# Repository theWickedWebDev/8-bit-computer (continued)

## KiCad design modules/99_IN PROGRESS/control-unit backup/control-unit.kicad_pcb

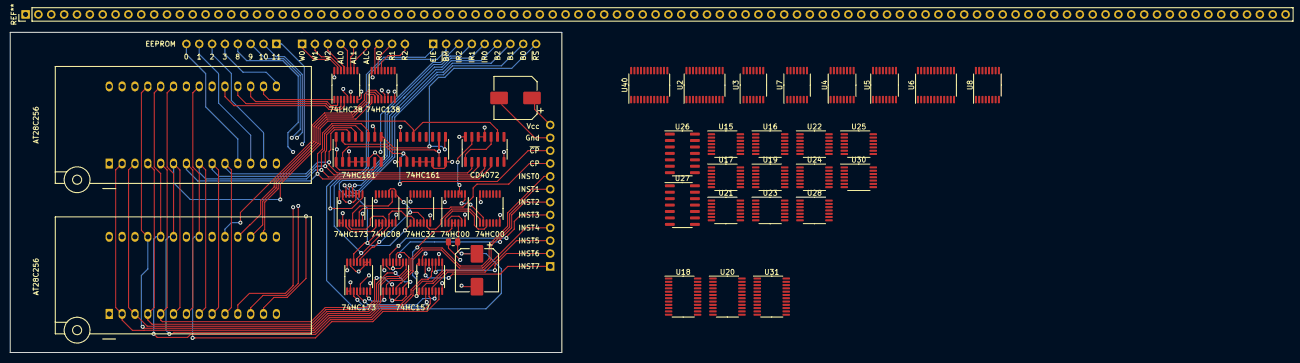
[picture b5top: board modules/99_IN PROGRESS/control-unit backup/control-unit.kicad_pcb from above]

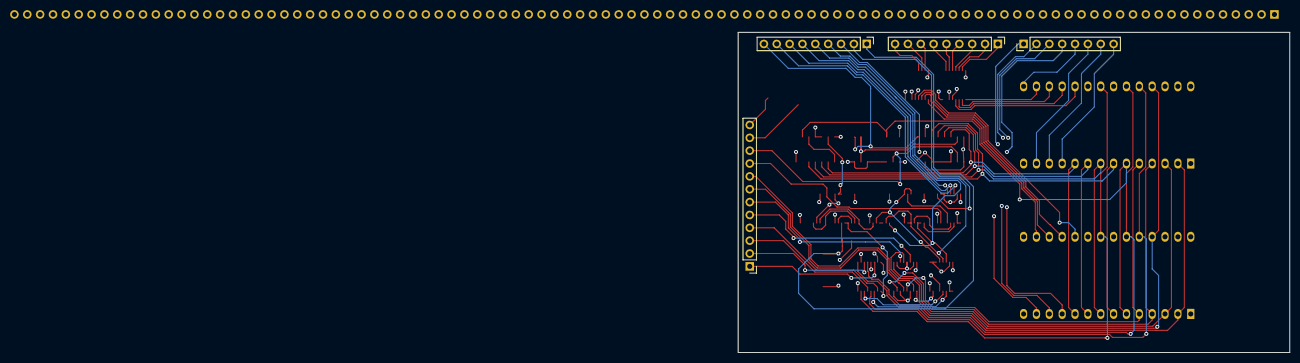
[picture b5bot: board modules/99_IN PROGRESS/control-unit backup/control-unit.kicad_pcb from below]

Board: 4 copper layers, 109.0 x 63.2 mm, 47 parts (4 on the bottom side), 140 nets.

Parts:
C1, C2: CP; CP_Elec_8x10
J1: Conn_01x08; PinHeader_1x08_P2.54mm_Vertical
J2, J3: Conn_01x09; PinHeader_1x09_P2.54mm_Vertical
J4: Conn_01x12; PinHeader_1x12_P2.54mm_Vertical
J5: Conn_01x99; 1x99_pinheader
R1: 3.9kohm; R_0805_2012Metric
U1, U15, U17, U37: 74LS00; TSSOP-14_4.4x5mm_P0.65mm
U2, U6, U18, U20, U31, U40: 74LS154; TSSOP-24_4.4x7.8mm_P0.65mm
U3, U23, U24, U25, U38: 74LS08; TSSOP-14_4.4x5mm_P0.65mm
U4, U5: 74LS258; TSSOP-16_4.4x5mm_P0.65mm
U7: 74HC04; TSSOP-14_4.4x5mm_P0.65mm
U8, U34, U35: 74LS157; TSSOP-16_4.4x5mm_P0.65mm
U9, U12: 28C256; DIP_Socket-28_W11.9_W12.7_W15.24_W17.78_W18.5_3M_228-1277-0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
U10, U11: 74LS161; SOIC-16_3.9x9.9mm_P1.27mm
U13, U14: 74LS138; TSSOP-16_4.4x5mm_P0.65mm
U16, U21: 74LS04; TSSOP-14_4.4x5mm_P0.65mm
U19, U28, U29, U30: 74LS32; TSSOP-14_4.4x5mm_P0.65mm
U22: 74LS86; TSSOP-14_4.4x5mm_P0.65mm
U26, U27, U33: CD4072; SOIC-14_3.9x8.7mm_P1.27mm
U36, U39: 74LS173; TSSOP-16_4.4x5mm_P0.65mm

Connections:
/Conditional Jumps/~JUMP: U6.2, U16.1
/Conditional Jumps/~JUMP_JA_JNBE: U6.13, U21.1
/Conditional Jumps/~JUMP_JBE_JNA: U6.11, U16.13
/Conditional Jumps/~JUMP_JB_JNAE_JC: U6.9, U16.11
/Conditional Jumps/~JUMP_JE_JZ: U6.7, U16.9
/Conditional Jumps/~JUMP_JGE_JNL: U6.15, U21.9
/Conditional Jumps/~JUMP_JG_JNLE: U6.17, U21.13
/Conditional Jumps/~JUMP_JLE_JNG: U6.16, U21.5
/Conditional Jumps/~JUMP_JL_JNG: U6.14, U21.3
/Conditional Jumps/~JUMP_JNB_JAE_JNC: U6.10, U15.12
/Conditional Jumps/~JUMP_JNE_JNZ: U6.8, U15.9
/Conditional Jumps/~JUMP_JNO: U6.4, U15.1
/Conditional Jumps/~JUMP_JNS: U6.6, U15.4
/Conditional Jumps/~JUMP_JO: U6.3, U16.3
/Conditional Jumps/~JUMP_JS: U6.5, U16.5
/GROUP 1/ALU_MODE: J3.4, U3.10, U13.12
/GROUP 1/EEPROM_0: J1.8, U2.23, U6.23, U8.2, U9.11, U40.23
/GROUP 1/EEPROM_1: J1.7, U2.22, U6.22, U8.5, U9.12, U40.22
/GROUP 1/EEPROM_2: J1.6, U2.21, U6.21, U8.11, U9.13, U40.21
/GROUP 1/EEPROM_3: J1.5, U2.20, U6.20, U8.14, U9.15, U40.20
/GROUP 1/SHA_SEL_00: U4.7, U5.7
/GROUP 1/SHA_SEL_01: U4.4, U5.4
/GROUP 1/~ALU_MODE_0_CARRY_IN_EN: J3.6, U3.4, U7.1, U13.10
/GROUP 1/~ALU_MODE_1_EN: J3.5, U3.9, U13.11
/GROUP 1/~WRITE_MUX0_EN: J3.1, U13.15, U40.18, U40.19
/GROUP 1/~WRITE_MUX1_EN: J3.2, U2.18, U2.19, U13.14
/GROUP 1/~WRITE_MUX2_EN: J3.3, U6.18, U6.19, U13.13
/GROUP 2/EEPROM_8: J1.4, U12.11, U18.23, U20.23, U31.23
/GROUP 2/EEPROM_9: J1.3, U12.12, U18.22, U20.22, U31.22
/GROUP 2/EEPROM_10: J1.2, U12.13, U18.21, U20.21, U31.21
/GROUP 2/EEPROM_11: J1.1, U12.15, U18.20, U20.20, U31.20
/GROUP 2/~READ_MUX0_EN: J3.7, U14.15, U18.18, U18.19
/GROUP 2/~READ_MUX1_EN: J3.8, U14.14, U20.18, U20.19
/GROUP 2/~READ_MUX2_EN: J3.9, U14.13, U31.18, U31.19
/MICROCODE EEPROM W/ COUNTER/BUS_0: J2.8, U36.14
/MICROCODE EEPROM W/ COUNTER/BUS_1: J2.7, U36.13
/MICROCODE EEPROM W/ COUNTER/BUS_2: J2.6, U36.12
/MICROCODE EEPROM W/ COUNTER/END_INTERRUPT_ENTER: C2.1, J2.1, R1.1, U37.5
/MICROCODE EEPROM W/ COUNTER/~SET_INT_ENABLE_BITMASK: J2.2, U36.9
CARRY_FLAG: U3.12, U15.13, U17.2, U19.2, U24.13
CLOCK: J4.9, U36.7
EEPROM_4: U9.16, U13.1
EEPROM_5: U9.17, U13.2
EEPROM_6: U9.18, U13.3
EEPROM_7: U9.19, U13.4
EEPROM_12: U12.16, U14.1
EEPROM_13: U12.17, U14.2
EEPROM_14: U12.18, U14.3
EEPROM_15: U12.19, U14.4
GND: C1.2, C2.2, J4.11, U1.7, U2.12, U3.7, U4.2, U4.6, U4.8, U4.10, U4.11, U4.13, U4.14, U5.3, U5.6, U5.8, U5.10, U5.11, U5.13, U5.14, U6.12, U7.7, U8.3, U8.6, U8.8, U8.10, U8.13, U8.15, U9.1, U9.14, U9.20, U9.22, U9.26, U10.3, U10.4, U10.5, U10.6, U10.8, U11.3, U11.4, U11.5, U11.6, U11.8, U12.14, U12.20, U12.22, U12.26, U13.5, U13.8, U14.5, U14.8, U15.7, U16.7, U17.7, U18.12, U19.7, U20.12, U21.7, U22.7, U23.7, U24.7, U25.7, U26.7, U27.7, U28.7, U29.7, U30.7, U31.12, U33.7, U33.11, U33.12, U34.3, U34.6, U34.8, U34.10, U34.13, U34.15, U35.8, U35.15, U36.1, U36.2, U36.8, U36.10, U36.11, U36.15, U37.7, U38.7, U39.1, U39.2, U39.8, U39.9, U39.10, U39.11, U39.15, U40.12
INSTRUCTION_0: J4.8, U34.2
INSTRUCTION_1: J4.7, U34.5
INSTRUCTION_2: J4.6, U34.11
INSTRUCTION_3: J4.5, U34.14
INSTRUCTION_4: J4.4, U35.2
INSTRUCTION_5: J4.3, U35.5
INSTRUCTION_6: J4.2, U35.11
INSTRUCTION_7: J4.1, U35.14
INST_0: U9.5, U12.5, U34.4
INST_1: U9.4, U12.4, U34.7
INST_2: U9.3, U12.3, U34.9
INST_3: U9.25, U12.25, U34.12
INST_4: U9.24, U12.24, U35.4
INST_5: U9.21, U12.21, U35.7
INST_6: U9.23, U12.23, U35.9
INST_7: U9.2, U12.2, U35.12
INTERRUPT_HANDLER_EN: U34.1, U35.1, U37.3, U37.4, U39.7
INTERRUPT_REQ_0: J2.5, U29.1, U38.2, U38.3, U39.14
INTERRUPT_REQ_0_ST: U35.3, U39.3
INTERRUPT_REQ_1: J2.4, U29.2, U38.5, U38.6, U39.13
INTERRUPT_REQ_1_ST: U35.6, U39.4
INTERRUPT_REQ_2: J2.3, U29.5, U38.8, U38.10, U39.12
INTERRUPT_REQ_2_ST: U35.10, U39.5
unnamed: U1.1, U29.6
unnamed: U1.2, U37.8
unnamed: U1.3, U37.1
unnamed: U3.3, U4.15
unnamed: U3.5, U3.8
unnamed: U3.6, U8.1
unnamed: U3.13, U7.2
unnamed: U10.15, U11.7, U11.10
unnamed: U15.3, U26.4
unnamed: U15.6, U26.9
unnamed: U15.8, U26.11
unnamed: U15.11, U27.2
unnamed: U16.2, U26.2
unnamed: U16.4, U23.1
unnamed: U16.6, U23.4
unnamed: U16.8, U23.9
unnamed: U16.10, U24.12
unnamed: U16.12, U24.1
unnamed: U17.3, U24.5
unnamed: U17.6, U19.5
unnamed: U19.3, U24.2
unnamed: U19.4, U23.11
unnamed: U19.6, U25.2, U25.4
unnamed: U19.8, U27.9
unnamed: U19.9, U22.3, U24.10
unnamed: U19.10, U21.6
unnamed: U21.2, U24.4
unnamed: U21.4, U24.9
unnamed: U21.8, U25.1
unnamed: U21.10, U25.5
unnamed: U21.12, U25.13
unnamed: U23.3, U26.3
unnamed: U23.6, U26.5
unnamed: U23.8, U26.10
unnamed: U24.3, U27.3
unnamed: U24.6, U27.4
unnamed: U24.8, U27.5
unnamed: U24.11, U26.12
unnamed: U25.3, U27.10
unnamed: U25.11, U27.11
unnamed: U25.6, U25.12
unnamed: U26.1, U28.1
unnamed: U26.13, U28.2
unnamed: U27.1, U27.12
unnamed: U27.13, U28.5
unnamed: U28.3, U28.4
unnamed: U29.3, U29.4
unnamed: U33.1, U33.10
unnamed: U33.13, U37.9, U37.10
unnamed: U36.3, U38.1
unnamed: U36.4, U38.4
unnamed: U36.5, U38.9
unnamed: U37.2, U37.6
OVERFLOW_FLAG: U15.2, U17.4, U22.2, U23.2, U23.12
SIGN_FLAG: U15.5, U17.5, U22.1, U23.5, U23.13
STEP_0: U9.10, U10.14, U12.10, U33.2
STEP_1: U9.9, U10.13, U12.9, U33.3
STEP_2: U9.8, U10.12, U12.8, U33.4
STEP_3: U9.7, U10.11, U12.7, U33.5
STEP_4: U9.6, U11.14, U12.6, U33.9
VCC: C1.1, J4.12, R1.2, U1.14, U2.24, U3.14, U4.3, U4.5, U4.16, U5.2, U5.5, U5.16, U6.24, U7.14, U8.16, U9.27, U9.28, U10.1, U10.7, U10.10, U10.16, U11.1, U11.16, U12.1, U12.27, U12.28, U13.6, U13.16, U14.6, U14.16, U15.14, U16.14, U17.14, U18.24, U19.14, U20.24, U21.14, U22.14, U23.14, U24.14, U25.14, U26.14, U27.14, U28.14, U29.14, U30.14, U31.24, U33.14, U34.16, U35.13, U35.16, U36.16, U37.14, U38.14, U39.16, U40.24
ZERO_FLAG: U15.10, U17.1, U19.1, U21.11, U23.10
~CLOCK: J4.10, U10.2, U11.2
~LOAD_A_REGISTER: U2.7, U5.1, U5.15
~RESET_STEP_COUNTER: J2.9, U10.9, U11.9
~SHIFT_A_LEFT: U2.8, U3.2
~SHIFT_A_RIGHT: U2.9, U3.1, U4.1

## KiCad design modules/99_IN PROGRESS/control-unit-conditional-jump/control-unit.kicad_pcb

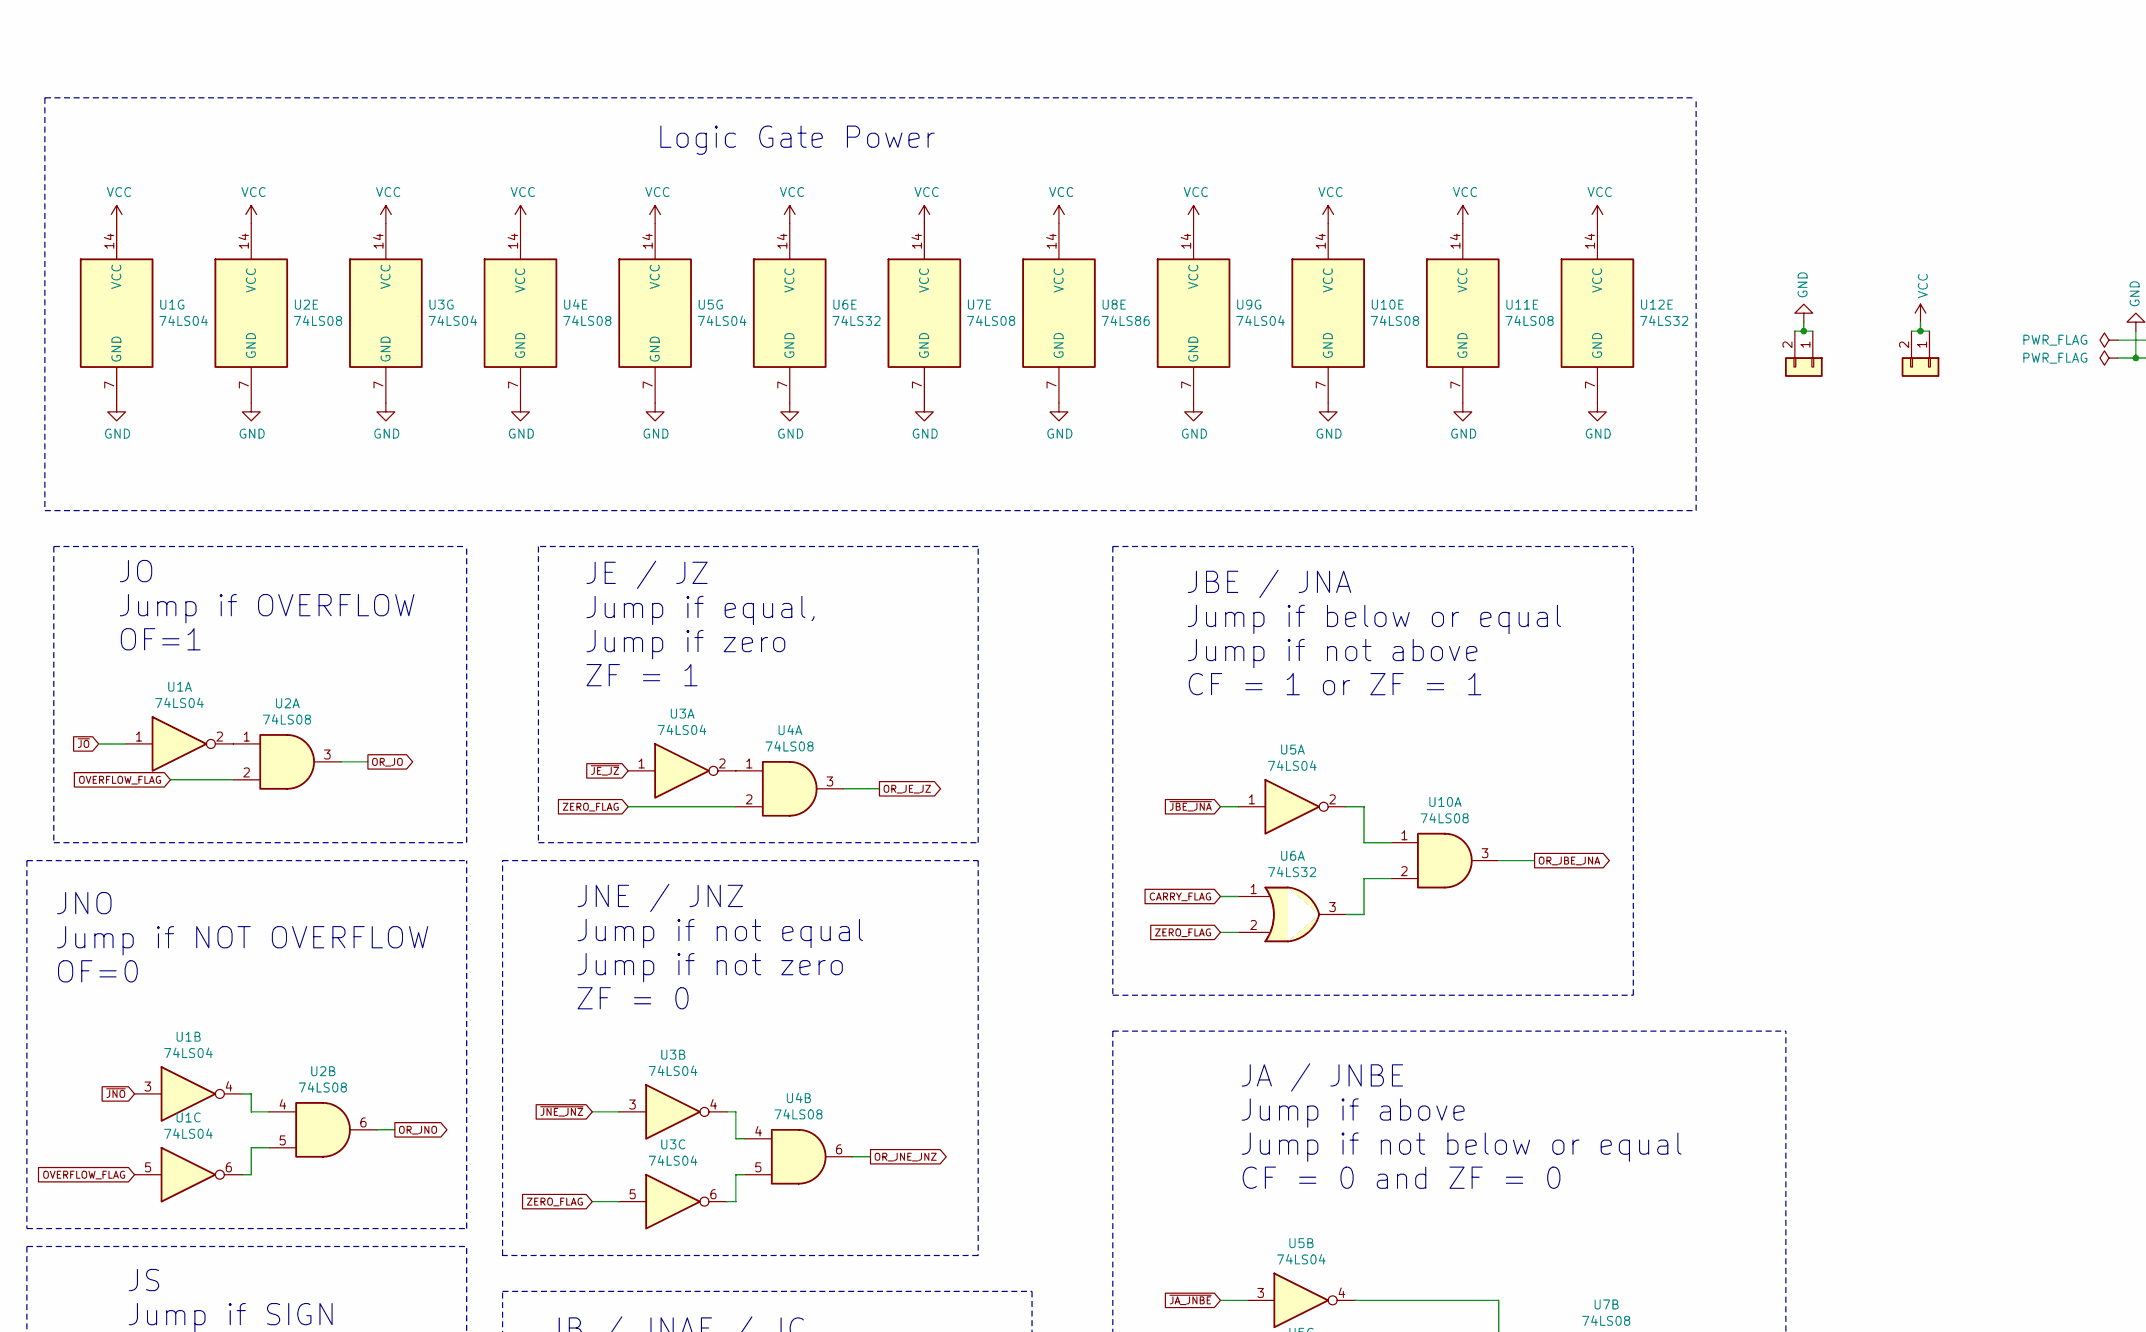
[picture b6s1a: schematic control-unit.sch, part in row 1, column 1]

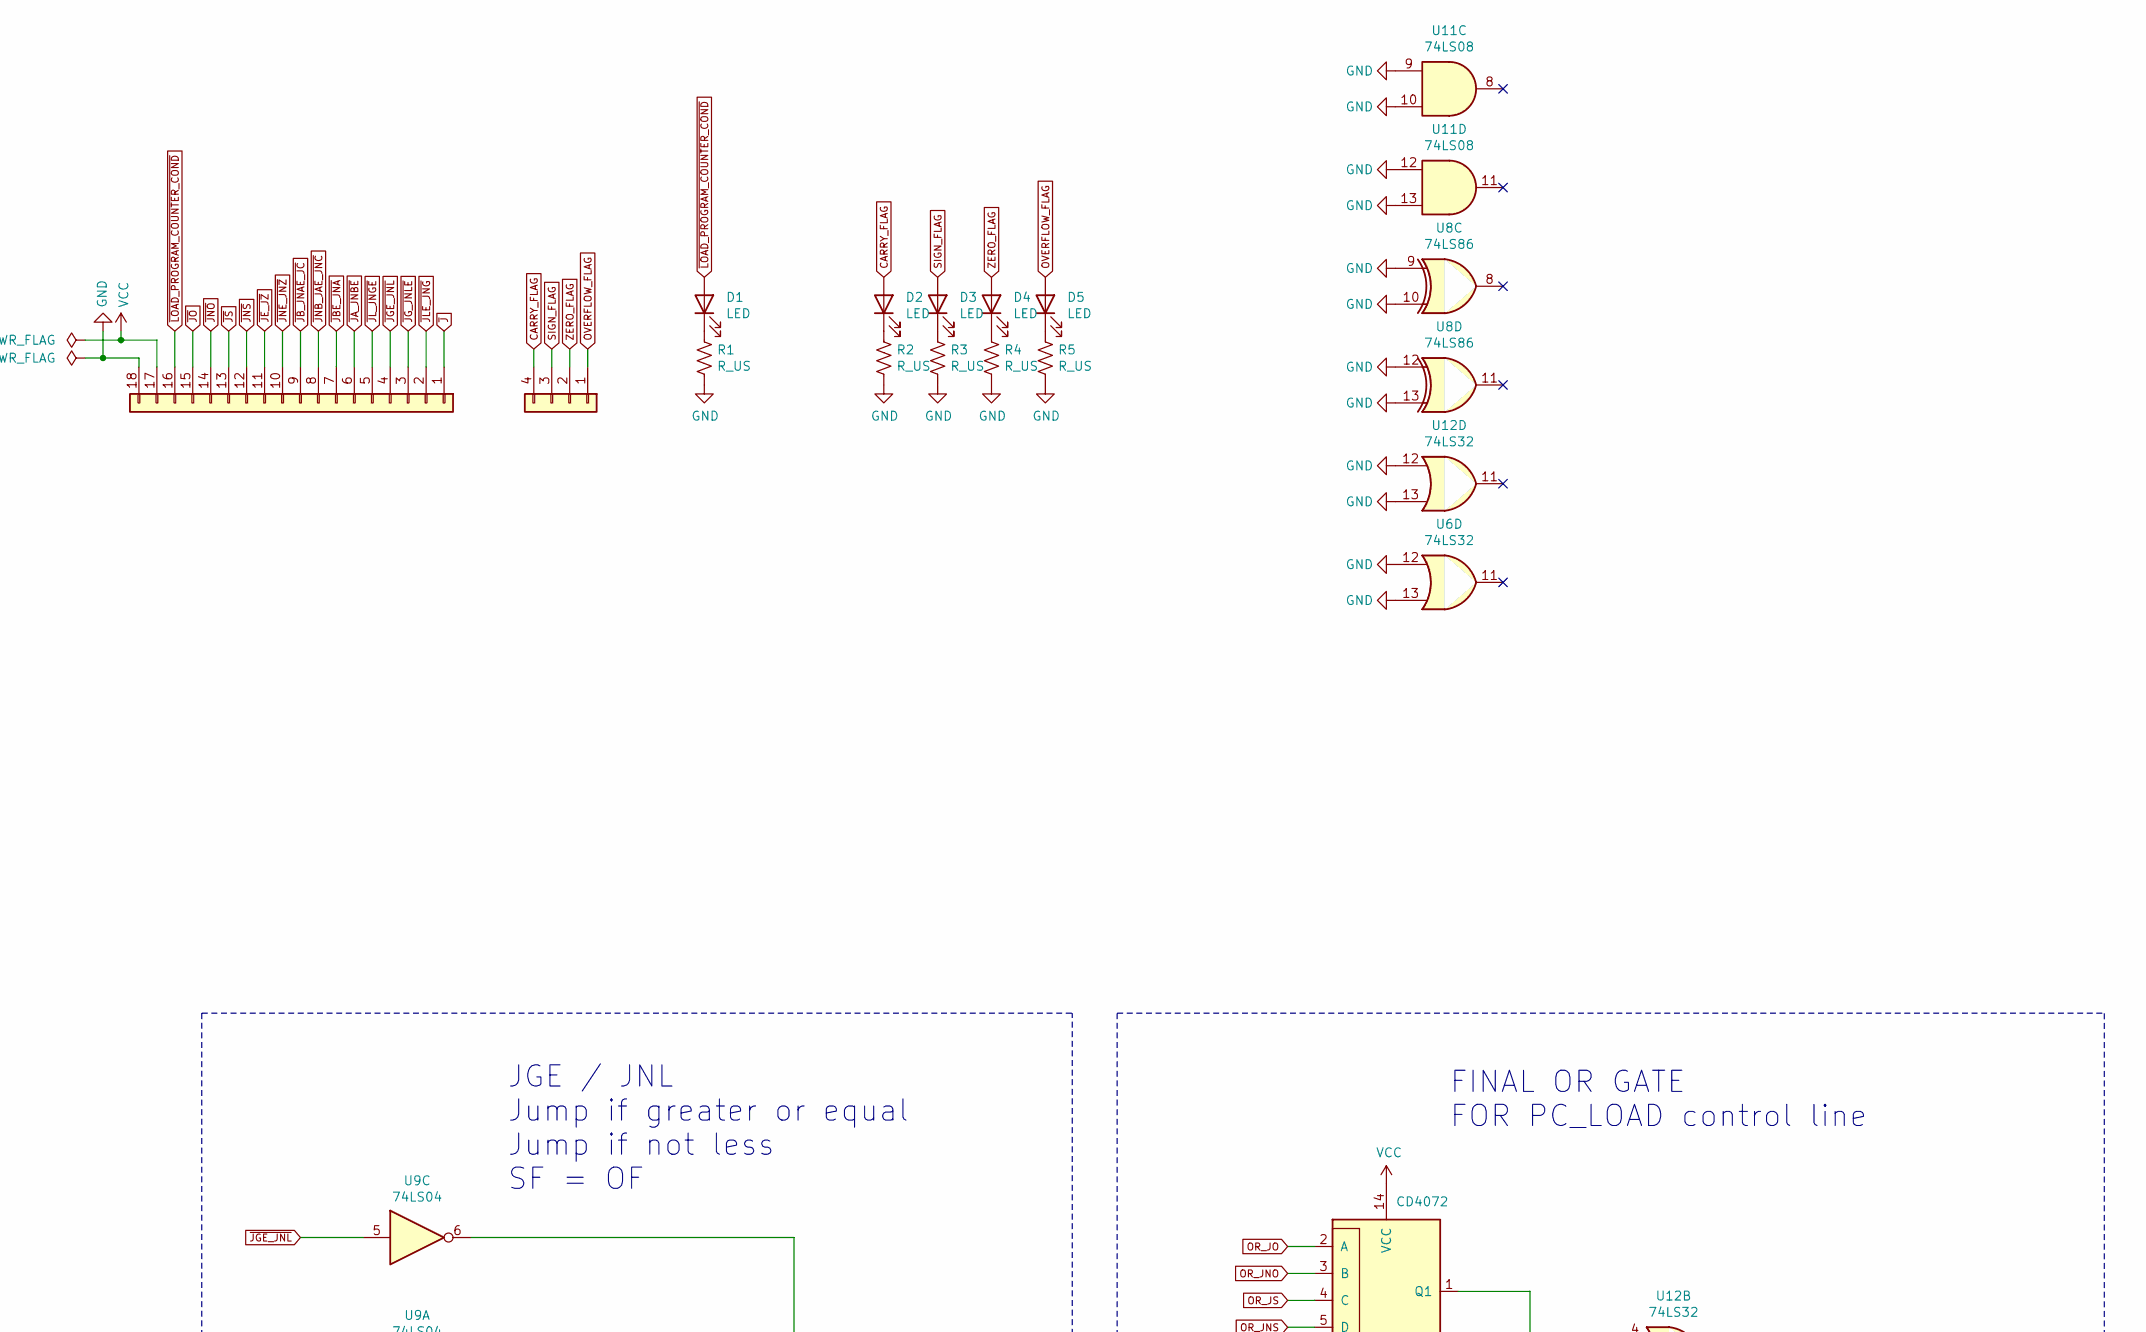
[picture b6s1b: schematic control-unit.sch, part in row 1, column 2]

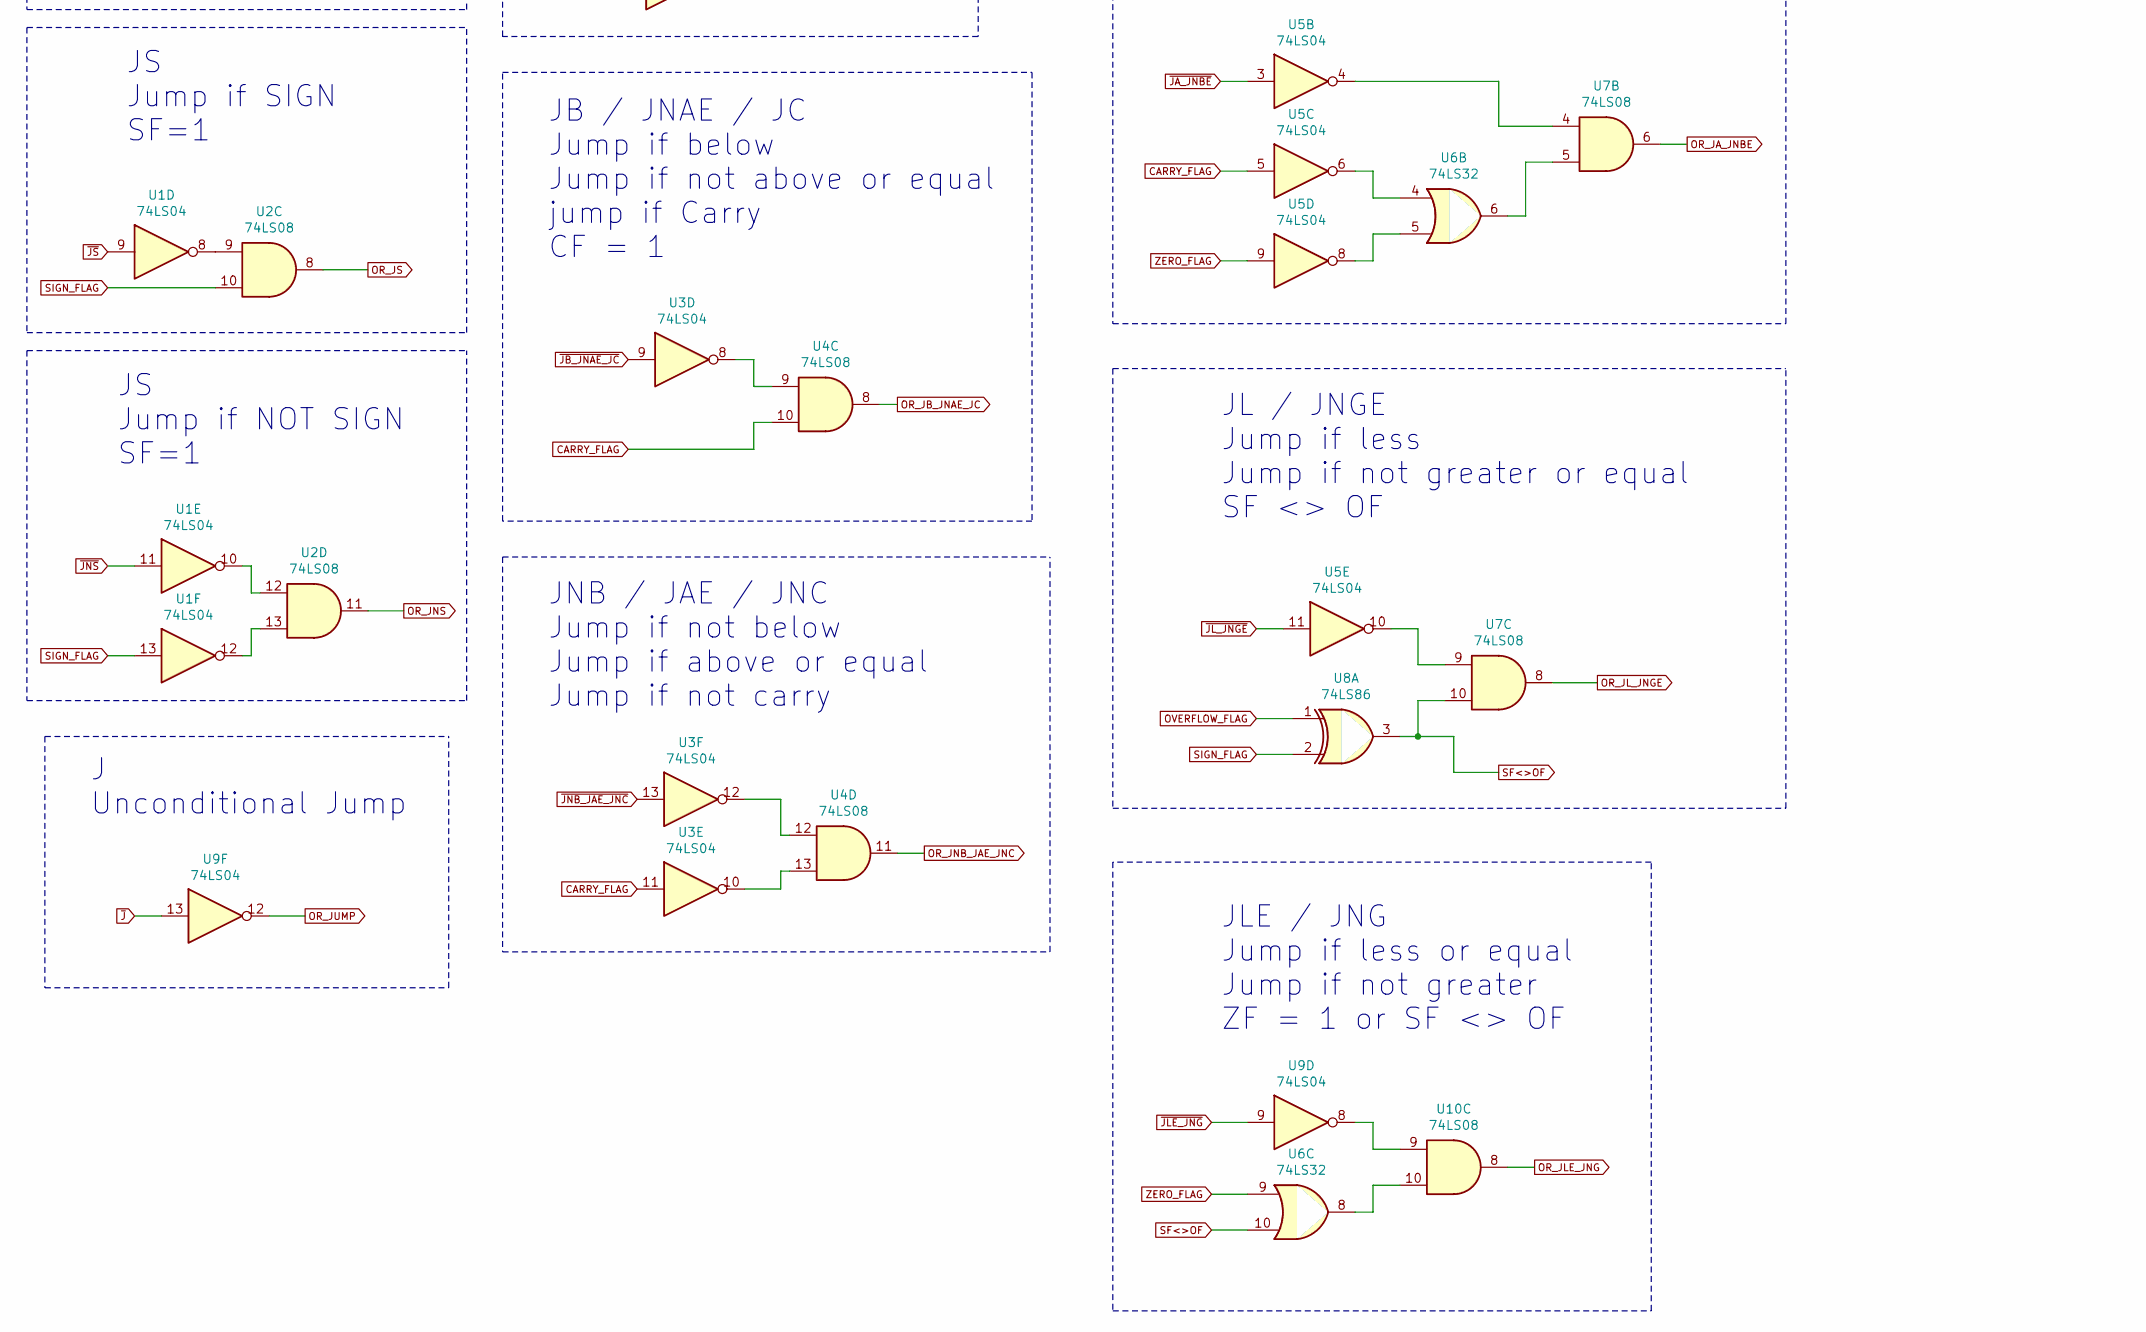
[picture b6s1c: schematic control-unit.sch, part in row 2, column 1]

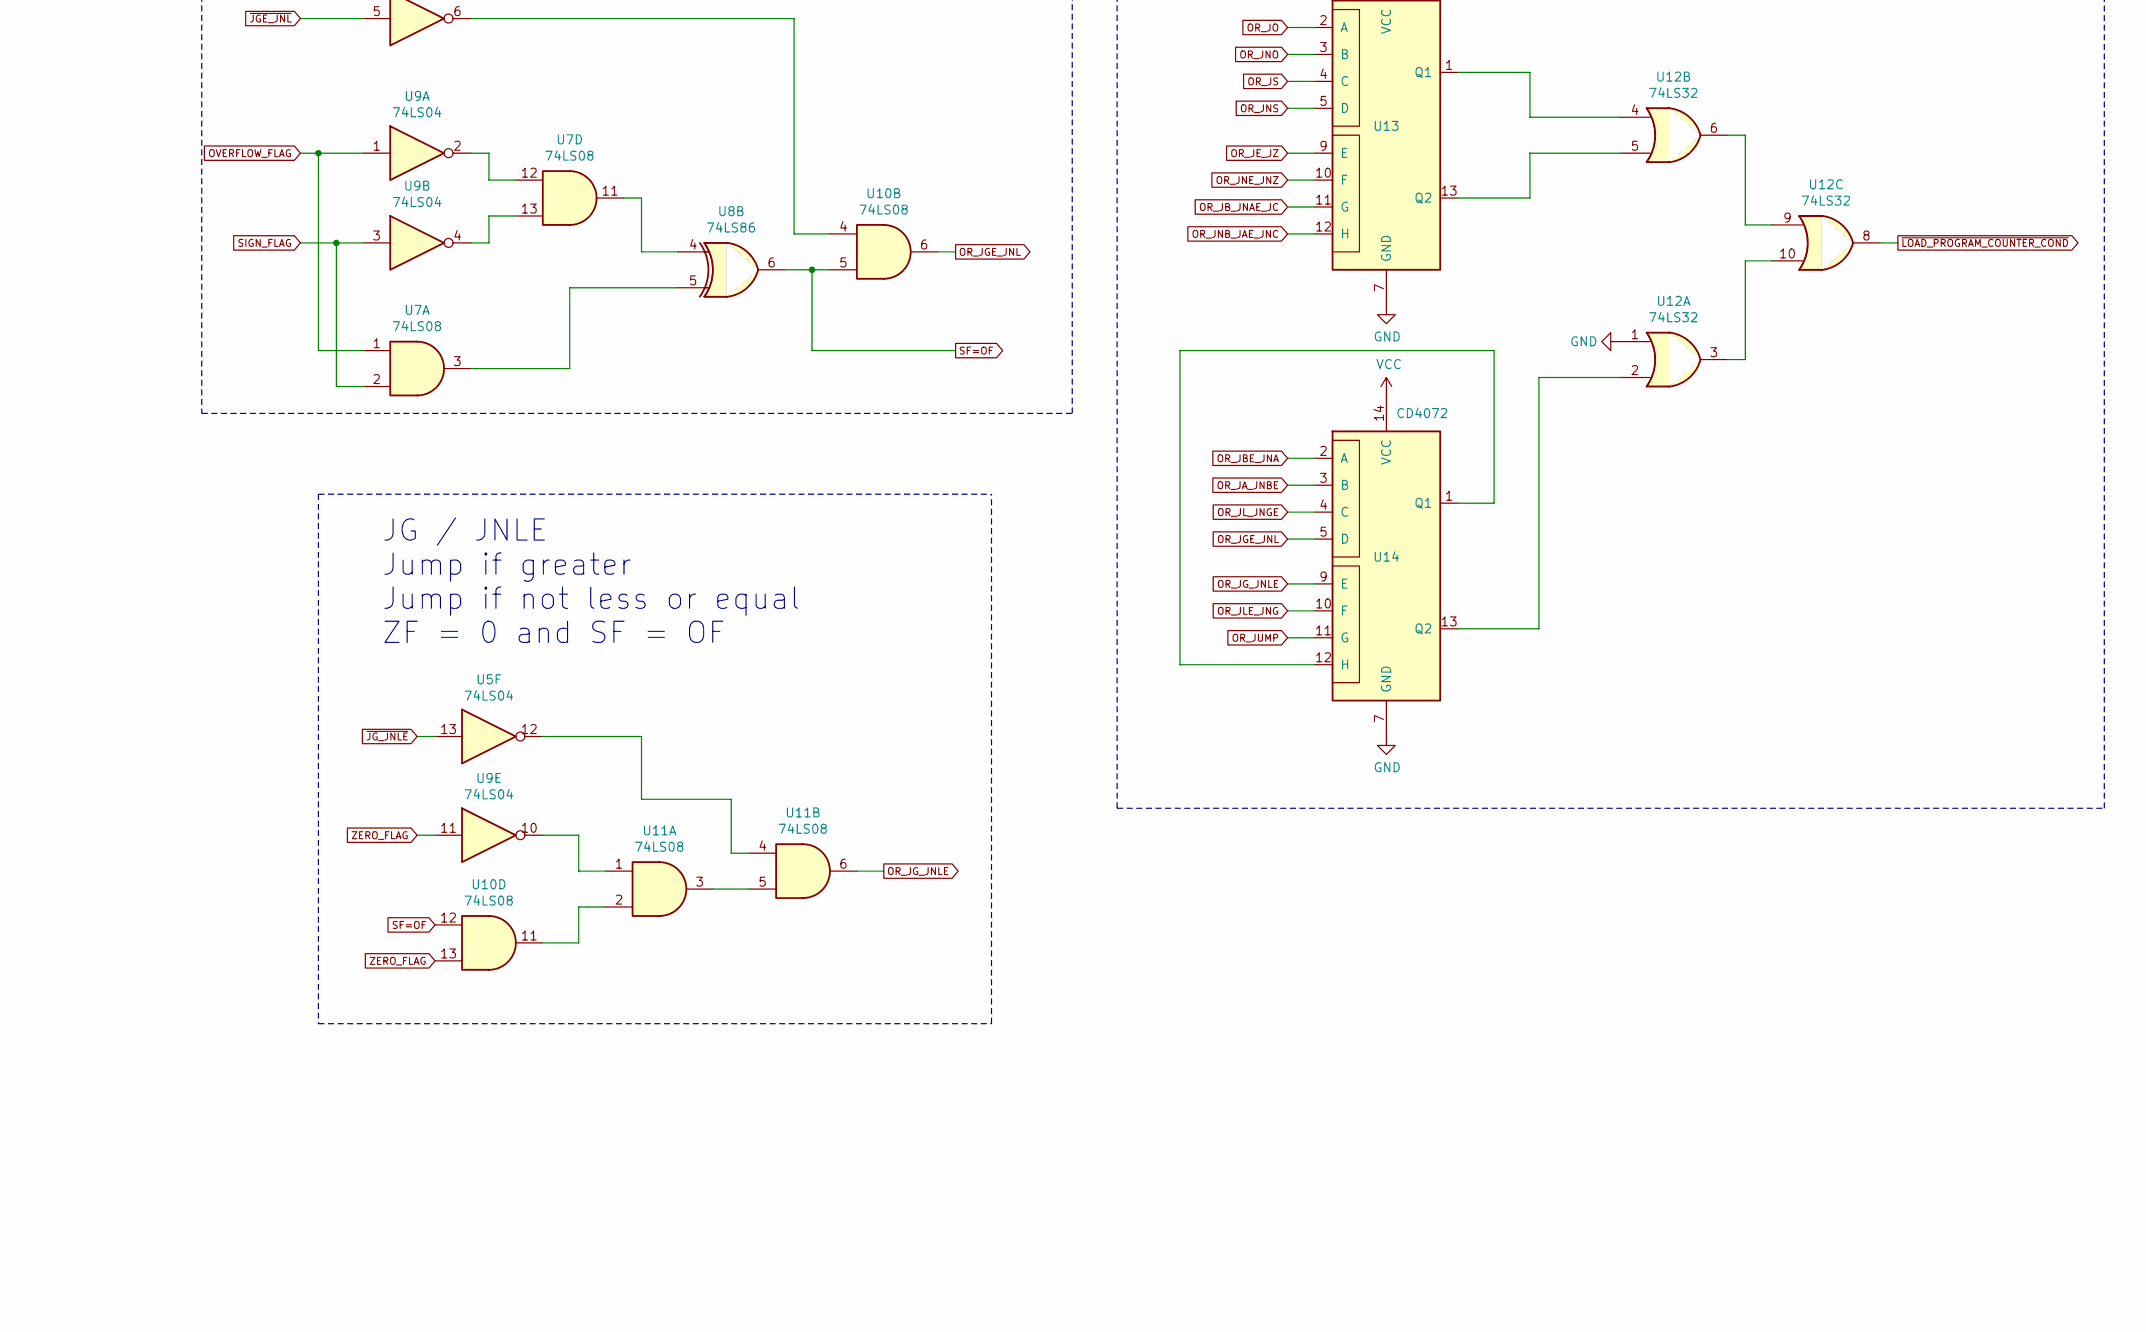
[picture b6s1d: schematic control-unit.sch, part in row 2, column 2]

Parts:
D1, D2, D3, D4, D5: LED; LED_0805_2012Metric
J1: Conn_01x04; PinHeader_1x04_P2.54mm_Vertical
J2: Conn_01x18; PinHeader_1x18_P2.54mm_Vertical
J3, J4: Conn_01x02; PinHeader_1x02_P2.54mm_Vertical
R1, R2, R3, R4, R5: R_US; R_0805_2012Metric
U1, U3, U5, U9: 74LS04; TSSOP-14_4.4x5mm_P0.65mm
U2, U4, U7, U10, U11: 74LS08; TSSOP-14_4.4x5mm_P0.65mm
U6, U12: 74LS32; TSSOP-14_4.4x5mm_P0.65mm
U8: 74LS86; TSSOP-14_4.4x5mm_P0.65mm
U13, U14: CD4072; SOIC-14_3.9x8.7mm_P1.27mm

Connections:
CARRY_FLAG: D2.2 (A), J1.4, U3.11, U4.10, U5.5, U6.1
GND: J2.18, J3.1, J3.2, R1.2, R2.2, R3.2, R4.2, R5.2, U1.7 (GND), U2.7 (GND), U3.7 (GND), U4.7 (GND), U5.7 (GND), U6.7 (GND), U6.12, U6.13, U7.7 (GND), U8.7 (GND), U8.9, U8.10, U8.12, U8.13, U9.7 (GND), U10.7 (GND), U11.7 (GND), U11.9, U11.10, U11.12, U11.13, U12.1, U12.7 (GND), U12.12, U12.13, U13.7 (GND), U14.7 (GND)
unnamed: D1.1 (K), R1.1
unnamed: D2.1 (K), R2.1
unnamed: D3.1 (K), R3.1
unnamed: D4.1 (K), R4.1
unnamed: D5.1 (K), R5.1
unnamed: U1.2, U2.1
unnamed: U1.4, U2.4
unnamed: U1.6, U2.5
unnamed: U1.8, U2.9
unnamed: U1.10, U2.12
unnamed: U1.12, U2.13
unnamed: U3.2, U4.1
unnamed: U3.4, U4.4
unnamed: U3.6, U4.5
unnamed: U3.8, U4.9
unnamed: U3.10, U4.13
unnamed: U3.12, U4.12
unnamed: U5.4, U7.4
unnamed: U5.6, U6.4
unnamed: U5.8, U6.5
unnamed: U5.10, U7.9
unnamed: U6.6, U7.5
unnamed: U7.3, U8.5
unnamed: U7.11, U8.4
unnamed: U7.12, U9.2
unnamed: U7.13, U9.4
unnamed: U5.2, U10.1
unnamed: U6.3, U10.2
unnamed: U9.6, U10.4
unnamed: U9.8, U10.9
unnamed: U6.8, U10.10
unnamed: U10.11, U11.2
unnamed: U9.10, U11.1
unnamed: U11.3, U11.5
unnamed: U5.12, U11.4
unnamed: U12.2, U14.13 (Q2)
unnamed: U12.4, U13.1 (Q1)
unnamed: U12.5, U13.13 (Q2)
unnamed: U12.6, U12.9
unnamed: U12.3, U12.10
unnamed: U14.1 (Q1), U14.12 (H)
OR_JA_JNBE: U7.6, U14.3 (B)
OR_JBE_JNA: U10.3, U14.2 (A)
OR_JB_JNAE_JC: U4.8, U13.11 (G)
OR_JE_JZ: U4.3, U13.9 (E)
OR_JGE_JNL: U10.6, U14.5 (D)
OR_JG_JNLE: U11.6, U14.9 (E)
OR_JLE_JNG: U10.8, U14.10 (F)
OR_JL_JNGE: U7.8, U14.4 (C)
OR_JNB_JAE_JNC: U4.11, U13.12 (H)
OR_JNE_JNZ: U4.6, U13.10 (F)
OR_JNO: U2.6, U13.3 (B)
OR_JNS: U2.11, U13.5 (D)
OR_JO: U2.3, U13.2 (A)
OR_JS: U2.8, U13.4 (C)
OR_JUMP: U9.12, U14.11 (G)
OVERFLOW_FLAG: D5.2 (A), J1.1, U1.5, U2.2, U7.1, U8.1, U9.1
SF<>OF: U6.10, U7.10, U8.3
SF=OF: U8.6, U10.5, U10.12
SIGN_FLAG: D3.2 (A), J1.3, U1.13, U2.10, U7.2, U8.2, U9.3
VCC: J2.17, J4.1, J4.2, U1.14 (VCC), U2.14 (VCC), U3.14 (VCC), U4.14 (VCC), U5.14 (VCC), U6.14 (VCC), U7.14 (VCC), U8.14 (VCC), U9.14 (VCC), U10.14 (VCC), U11.14 (VCC), U12.14 (VCC), U13.14 (VCC), U14.14 (VCC)
ZERO_FLAG: D4.2 (A), J1.2, U3.5, U4.2, U5.9, U6.2, U6.9, U9.11, U10.13
~J: J2.1, U9.13
~JA_JNBE: J2.6, U5.3
~JBE_JNA: J2.7, U5.1
~JB_JNAE_JC: J2.9, U3.9
~JE_JZ: J2.11, U3.1
~JGE_JNL: J2.4, U9.5
~JG_JNLE: J2.3, U5.13
~JLE_JNG: J2.2, U9.9
~JL_JNGE: J2.5, U5.11
~JNB_JAE_JNC: J2.8, U3.13
~JNE_JNZ: J2.10, U3.3
~JNO: J2.14, U1.3
~JNS: J2.12, U1.11
~JO: J2.15, U1.1
~JS: J2.13, U1.9
~LOAD_PROGRAM_COUNTER_COND: D1.2 (A), J2.16, U12.8

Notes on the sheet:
JO Jump if OVERFLOW OF=1
JNO Jump if NOT OVERFLOW OF=0
JS Jump if SIGN SF=1
JS Jump if NOT SIGN SF=1
JE / JZ Jump if equal, Jump if zero ZF = 1
JNE / JNZ Jump if not equal Jump if not zero ZF = 0
JB / JNAE / JC Jump if below Jump if not above or equal jump if Carry CF = 1
JNB / JAE / JNC Jump if not below Jump if above or equal Jump if not carry
JBE / JNA Jump if below or equal Jump if not above CF = 1 or ZF = 1
JA / JNBE Jump if above Jump if not below or equal CF = 0 and ZF = 0
JL / JNGE Jump if less Jump if not greater or equal SF <> OF
JGE / JNL Jump if greater or equal Jump if not less SF = OF
JLE / JNG Jump if less or equal Jump if not greater ZF = 1 or SF <> OF
JG / JNLE Jump if greater Jump if not less or equal ZF = 0 and SF = OF
Logic Gate Power
J Unconditional Jump
FINAL OR GATE FOR PC_LOAD control line

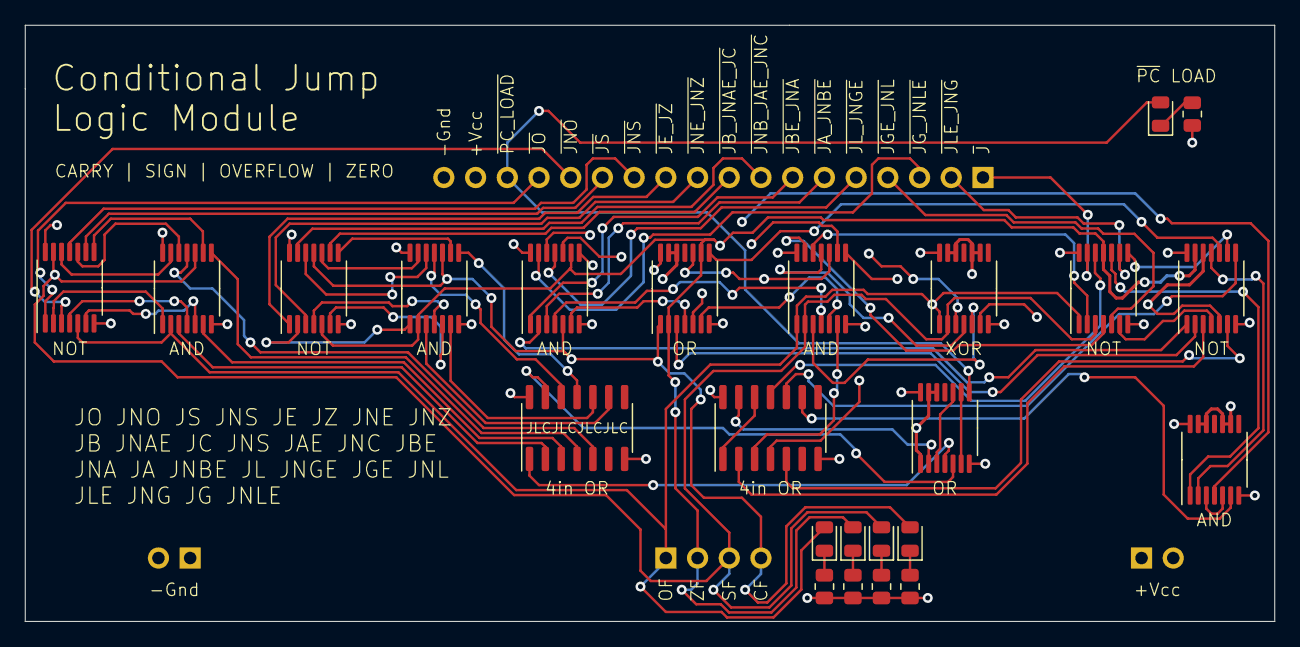
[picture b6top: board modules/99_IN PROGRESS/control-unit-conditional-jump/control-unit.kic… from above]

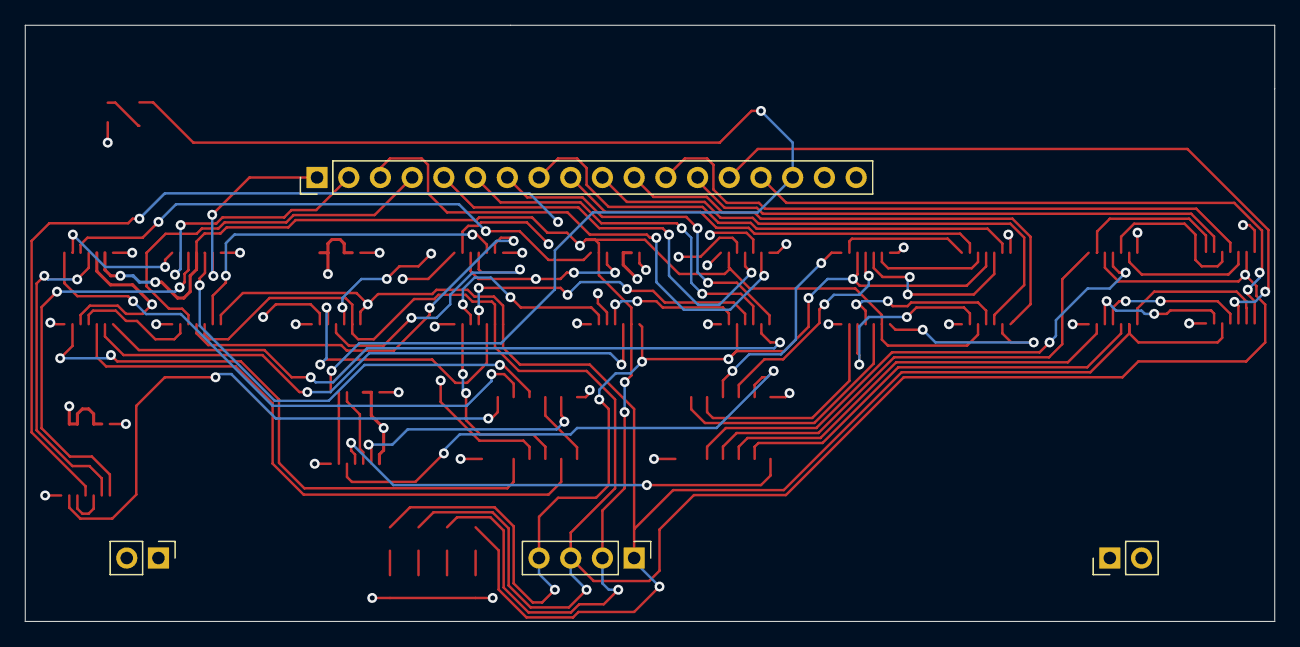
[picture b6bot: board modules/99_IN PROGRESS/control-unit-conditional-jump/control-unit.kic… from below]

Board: 4 copper layers, 100.1 x 47.8 mm, 28 parts (4 on the bottom side), 80 nets.
